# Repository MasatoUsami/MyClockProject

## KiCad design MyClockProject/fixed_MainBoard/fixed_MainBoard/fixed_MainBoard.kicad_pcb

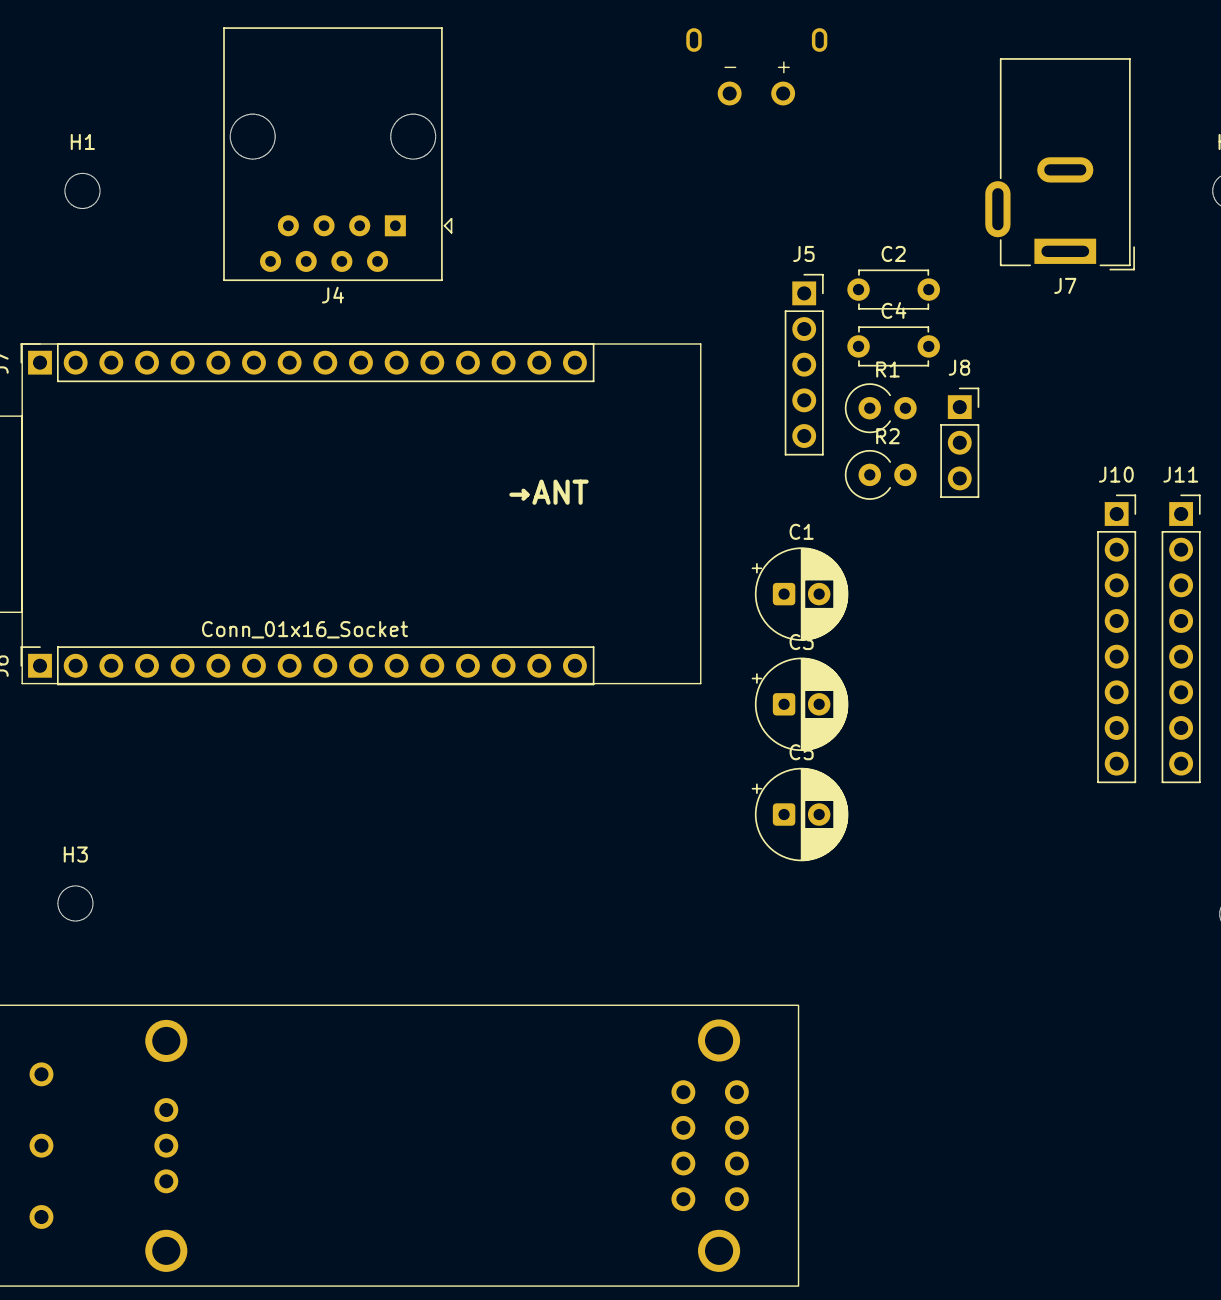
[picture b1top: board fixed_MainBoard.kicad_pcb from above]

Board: 2 copper layers, 20 parts (0 on the bottom side), 7 nets, no tracks yet.

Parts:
C1, C5: 100u; CP_Radial_D6.3mm_P2.50mm
C2, C4: 0.1u; C_Disc_D4.7mm_W2.5mm_P5.00mm
C3: 470u; CP_Radial_D6.3mm_P2.50mm
H1, H2, H3, H4: MountingHole; MountingHole_2.5mm
J3: USB_C_Receptacle_PowerOnly_6P; USB_C_Receptacle_GCT_USB4125-xx-x-0190_6P_TopMnt_Horizontal
J4: RJ45; RJ45_Amphenol_54602-x08_Horizontal
J5: Conn_01x05_Socket; PinSocket_1x05_P2.54mm_Vertical
J6: Conn_01x16_Socket; PinSocket_1x16_P2.54mm_Vertical
J7: Conn_01x08_Socket; PinSocket_1x16_P2.54mm_Vertical
J7#2: Barrel_Jack; BarrelJack_Wuerth_6941xx301002
J8: Conn_01x03_Socket; PinSocket_1x03_P2.54mm_Vertical
J10, J11: Conn_01x08_Socket; PinSocket_1x08_P2.54mm_Vertical
R1: 120Ω; R_Axial_DIN0309_L9.0mm_D3.2mm_P2.54mm_Vertical
R2: 10K; R_Axial_DIN0309_L9.0mm_D3.2mm_P2.54mm_Vertical

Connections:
GND: C2.2, C3.2, C4.2, C5.2, J4.7, J4.8, J6.GND (Pin_1_1), J7.GND, J7#2.2, J8.2
unnamed: C1.2, C2.1
unnamed: J8.1, R2.1
unnamed: J8.3, R2.2
unnamed: C3.1, C4.1, C5.1, J5.5, J7#2.1
unnamed: J4.1, R1.2
unnamed: J4.2, R1.1

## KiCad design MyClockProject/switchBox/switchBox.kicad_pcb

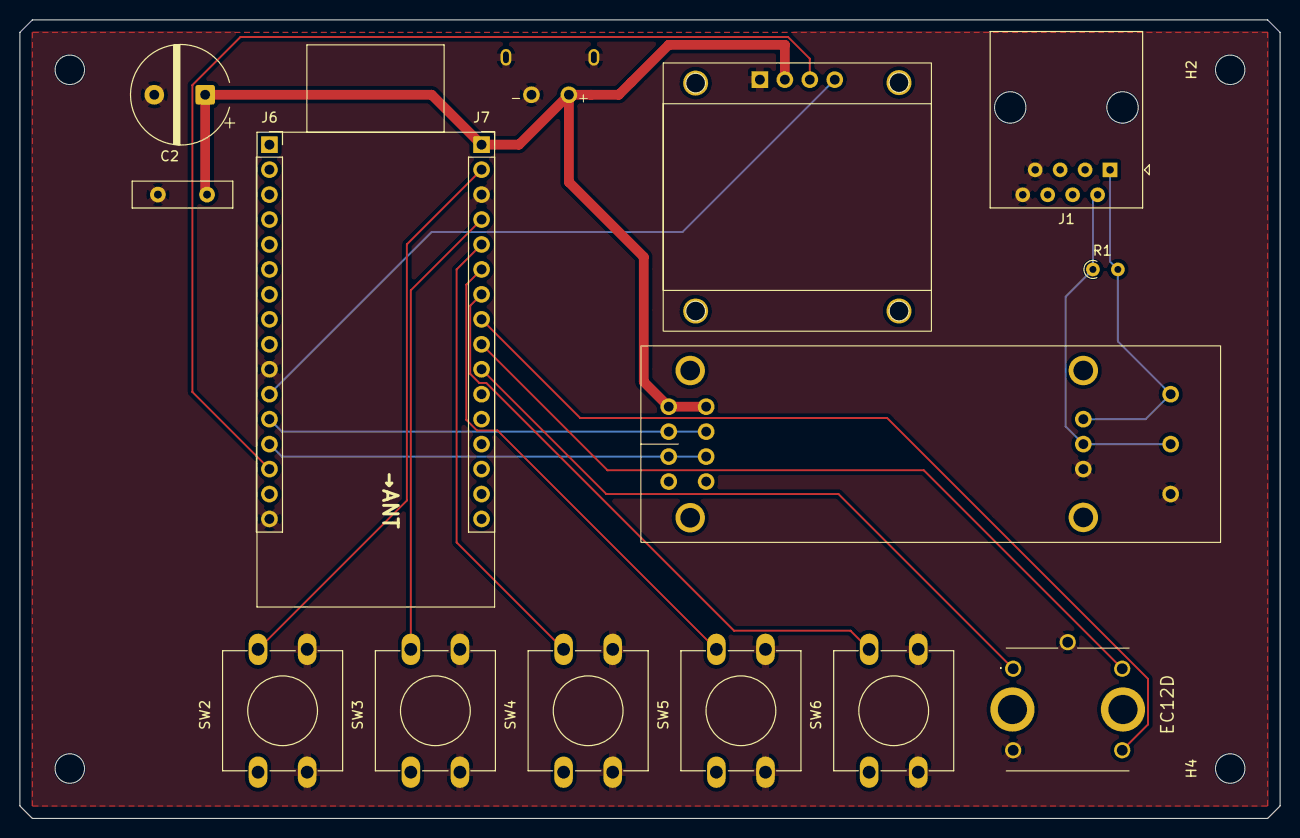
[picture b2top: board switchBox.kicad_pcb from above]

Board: 2 copper layers, 128.3 x 81.3 mm, 19 parts (0 on the bottom side), 16 nets.

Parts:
C1: .01u; C_Disc_D10.0mm_W2.5mm_P5.00mm
C2: 470u; CP_Radial_D10.0mm_P7.50mm
H1, H2, H3, H4: MountingHole; MountingHole_3mm
J1: RJ45; RJ45_Amphenol_54602-x08_Horizontal
J6: Conn_01x16_Socket; PinSocket_1x16_P2.54mm_Vertical
J7: Conn_01x08_Socket; PinSocket_1x16_P2.54mm_Vertical
R1: 120Ω; R_Axial_DIN0204_L3.6mm_D1.6mm_P1.90mm_Vertical
RS485toTTL5V_MAX1348_SH-U12: d20c897a-e8f7-4042-81bd-1f98a1eacd4c
RotaryEncoder: EC12D; 1481b7bd-967a-4c6f-926d-5fc3a8d29f51
SW2: S4_SW_Push; SW_PUSH-12mm
SW3: S3_SW_Push; SW_PUSH-12mm
SW4: S2_SW_Push; SW_PUSH-12mm
SW5: S1_SW_Push; SW_PUSH-12mm
SW6: MODE_SW_Push; SW_PUSH-12mm
U1: USB_C_Receptacle_PowerOnly_6P; USB_C_Receptacle_GCT_USB4125-xx-x-0190_6P_TopMnt_Horizontal
U4: OLED_SSD1306_128x32_I2C; Adafruit_SSD1306_I2c

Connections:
/Net-(J7-Pin_12): J7.12, SW3.1
/Net-(J7-Pin_13): J7.13, SW2.1
/Net-(J7-Pin_14): J7.14, SW4.1
/Net-(J7-Pin_26): J7.26, SW6.1
/Net-(J7-Pin_27): J7.27, SW5.1
/Net-(J7-Pin_32): J7.32, RotaryEncoder.A1
/Net-(J7-Pin_33): J7.33, RotaryEncoder.B1
/Net-(J7_Pin_25): J7.25, RotaryEncoder.D1
GND: C1.2, C2.2, J1.7, J1.8, J6.GND (Pin_1_1), J7.GND, RS485toTTL5V_MAX1348_SH-U12.GND, RotaryEncoder.C1, RotaryEncoder.E1, SW2.2, SW3.2, SW4.2, SW5.2, SW6.2, U1.5, U1.SH (SHIELD_SH), U4.GND
unnamed: J1.1, R1.2, RS485toTTL5V_MAX1348_SH-U12.A+
unnamed: J1.2, R1.1, RS485toTTL5V_MAX1348_SH-U12.B-
unnamed: J6.21 (Pin_11_11), U4.SDA
unnamed: J6.22 (Pin_14_14), U4.SCL
unnamed: J6.RXI (Pin_12_12), RS485toTTL5V_MAX1348_SH-U12.TXD
unnamed: J6.TXO (Pin_13_13), RS485toTTL5V_MAX1348_SH-U12.RXD
unnamed: C1.1, C2.1, J7.5V, RS485toTTL5V_MAX1348_SH-U12.5VO, U1.6, U4.VCC

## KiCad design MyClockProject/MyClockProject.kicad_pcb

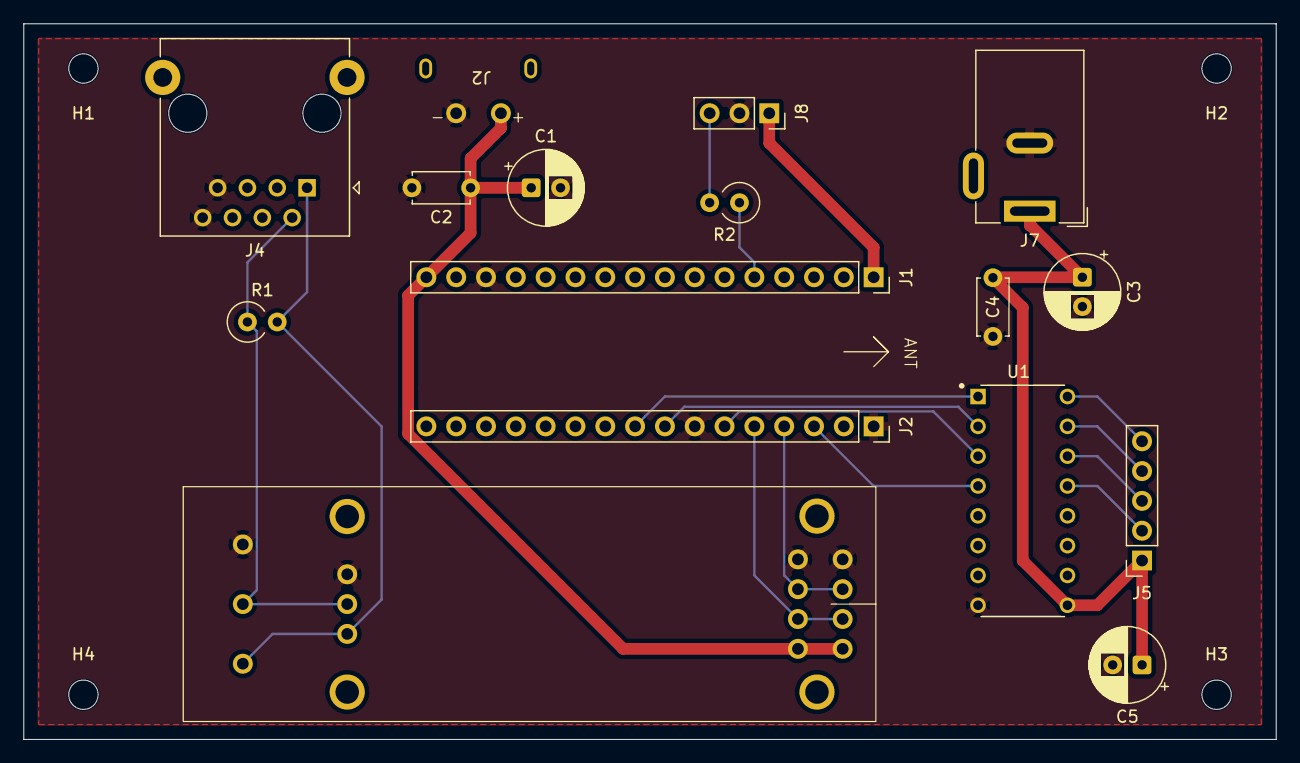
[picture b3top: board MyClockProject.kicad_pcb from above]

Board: 2 copper layers, 106.7 x 61.0 mm, 19 parts (0 on the bottom side), 16 nets.

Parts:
C1, C5: 100u; CP_Radial_D6.3mm_P2.50mm
C2, C4: 0.1u; C_Disc_D4.7mm_W2.5mm_P5.00mm
C3: 470u; CP_Radial_D6.3mm_P2.50mm
H1, H2, H3, H4: MountingHole; MountingHole_2.5mm
J1, J2#2: Conn_01x16_Socket_ESP32; PinSocket_1x16_P2.54mm_Vertical
J2: USB_C_Receptacle_PowerOnly_6P; USB_C_Receptacle_GCT_USB4125-xx-x-0190_6P_TopMnt_Horizontal
J4: RJ45; RJ45_RCH_RC01937
J5: Conn_01x05_Socket; PinSocket_1x05_P2.54mm_Vertical
J7: Barrel_Jack; BarrelJack_Wuerth_6941xx301002
J8: Conn_01x03_Socket; PinSocket_1x03_P2.54mm_Vertical
R1: 120Ω; R_Axial_DIN0309_L9.0mm_D3.2mm_P2.54mm_Vertical
R2: 10K; R_Axial_DIN0309_L9.0mm_D3.2mm_P2.54mm_Vertical
U1: ULN2003A

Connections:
GND: C1.2, C2.2, C3.2, C4.2, C5.2, J1.GND (Pin_14), J2.5, J2#2.GND (Pin_7), J4.7, J4.8, J7.2, J8.2, U1.8 (GND)
unnamed: J1.3V3 (Pin_1), J8.1
unnamed: J1.34 (Pin_6), R2.1
unnamed: C1.1, C2.1, J1.5V, J2.6
unnamed: J2#2.19 (Pin_8), U1.2 (I2)
unnamed: J2#2.21 (Pin_6), U1.3 (I3)
unnamed: J2#2.22 (Pin_3), U1.4 (I4)
unnamed: J2#2.18 (Pin_9), U1.1 (I1)
unnamed: C3.1, C4.1, C5.1, J5.1, J7.1, U1.9 (COM)
unnamed: J8.3, R2.2
unnamed: J5.2, U1.13 (O4)
unnamed: J5.3, U1.14 (O3)
unnamed: J5.4, U1.15 (O2)
unnamed: J5.5, U1.16 (O1)
unnamed: J4.1, R1.2
unnamed: J4.2, R1.1

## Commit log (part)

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2026-06-05 新しく自動時計用ファイルを設定します。現在はKiCad用mainBoardファイルの作業中です
2026-06-09 基盤を完成しました。５Vからのコンデンサの配線を修正しました。ホールセンサーを接続できるようにしました。
2026-06-23 SwitchBox と mainBoard の回路基板のFactory Dataを追加しました。
